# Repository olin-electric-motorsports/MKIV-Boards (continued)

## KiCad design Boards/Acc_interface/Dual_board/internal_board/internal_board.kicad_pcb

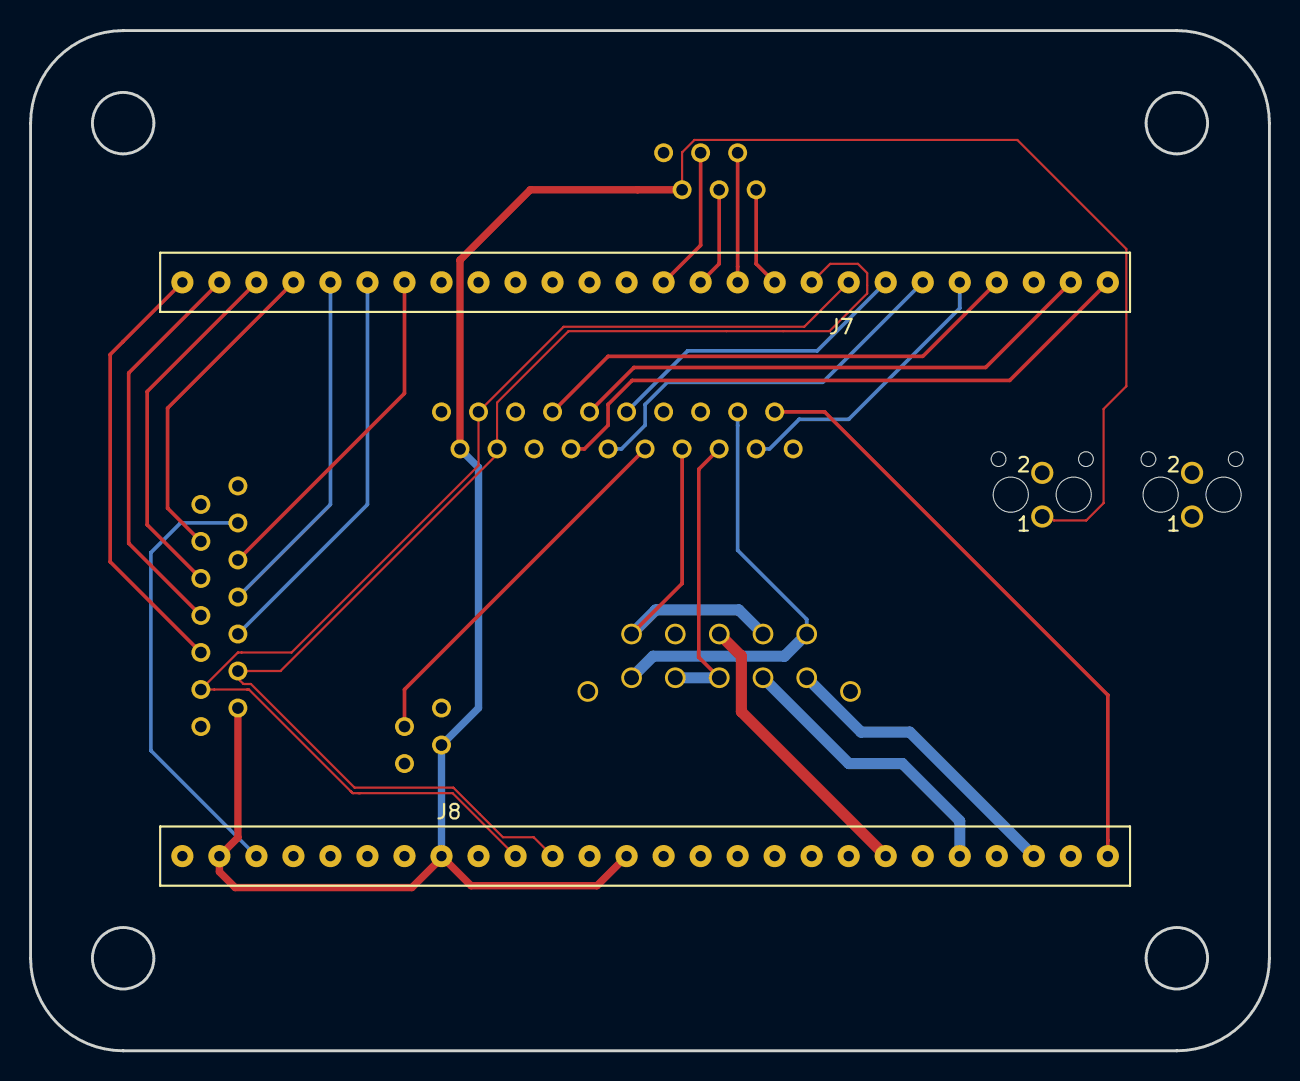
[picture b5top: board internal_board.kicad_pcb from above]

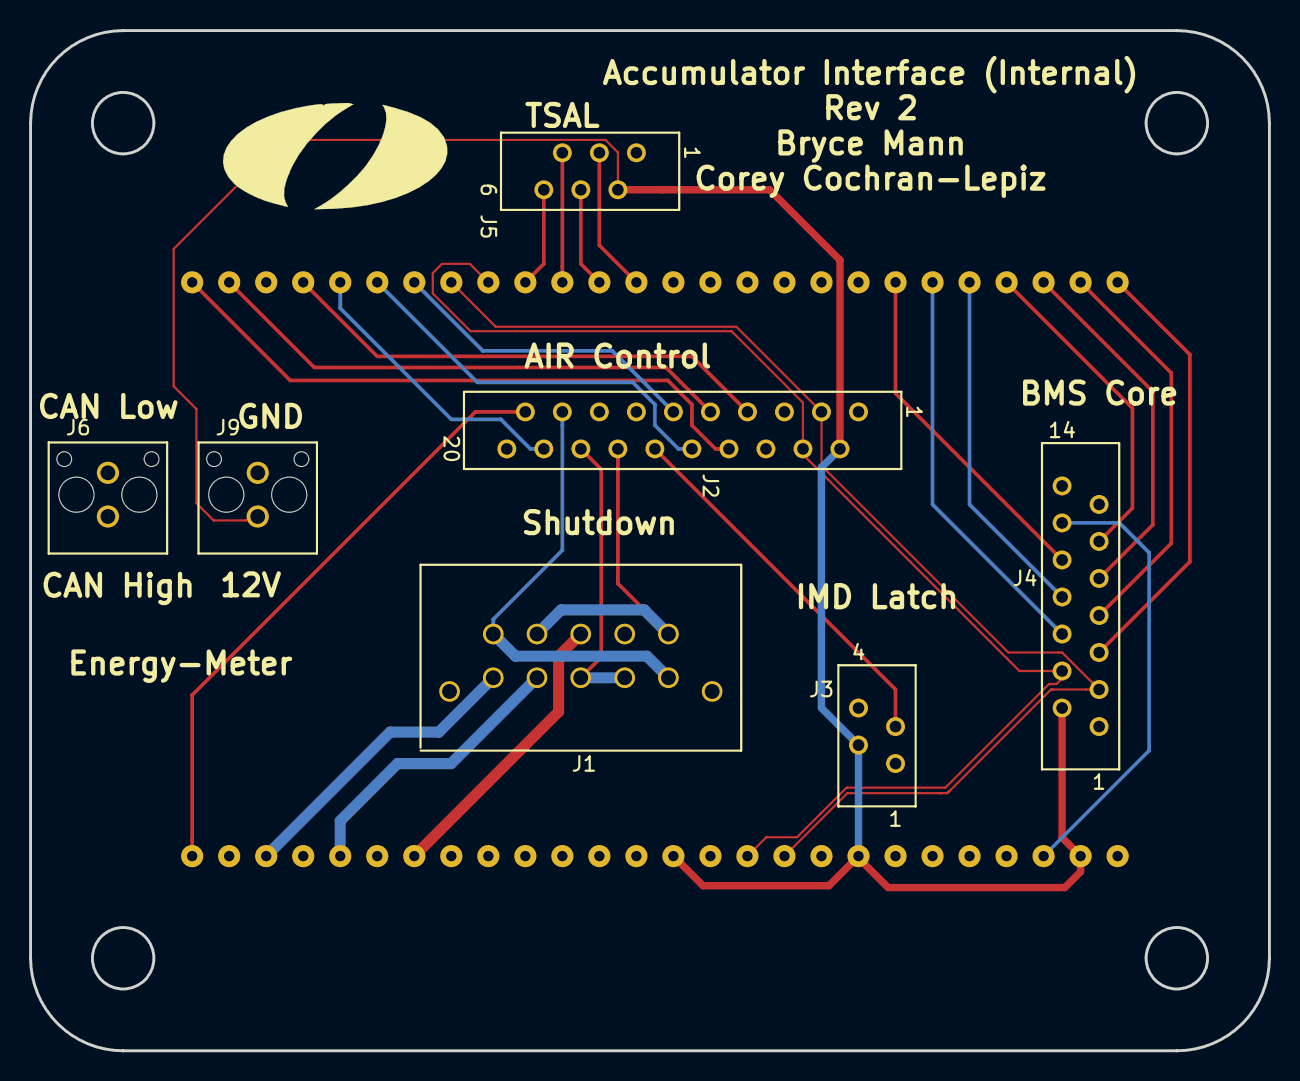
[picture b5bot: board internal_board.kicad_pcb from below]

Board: 4 copper layers, 85.0 x 70.0 mm, 9 parts (7 on the bottom side), 35 nets.

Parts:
J1: MicroFit_VT_10
J2: MM_F_RA_20; micromatch_female_ra_20
J3: MM_F_RA_04; micromatch_female_ra_4
J4: MM_F_RA_14; micromatch_female_ra_14
J5: MM_F_RA_06; micromatch_female_ra_6
J6, J9: MicroFit_V_2
J7, J8: SS-126-G-2; 26pos_screwsocket_.1in

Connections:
/5V_AIR: J2.5, J2.18, J7.5, J8.16
/5V_BMS: J4.5, J7.26
/12V: J2.2, J3.2, J4.2, J5.2, J8.2, J8.8, J8.13, J9.1
/BMS_SENSE: J2.13, J4.13
/BSPD_Current_sense: J4.14, J8.4
/CAN_HIGH: J2.3, J4.3, J7.8, J8.10
/CAN_LOW: J2.4, J4.4, J7.9, J8.11
/Cooling_pressure_sense: J2.19, J8.26
/FAN_PWM: J4.12, J8.3
/IMD_SENSE: J2.12, J3.3
/LED1_AIR: J2.10, J7.6
/LED1_BMS: J4.10, J7.20
/LED2_AIR: J2.11, J7.7
/LED2_BMS: J4.11, J7.23
/MISO_AIR: J2.7, J7.4
/MISO_BMS: J4.7, J7.25
/MOSI_AIR: J2.6, J7.3
/MOSI_BMS: J4.6, J7.21
/RESET_AIR: J2.9, J7.2
/RESET_BMS: J4.9, J7.24
/SCK_AIR: J2.8, J7.1
/SCK_BMS: J4.8, J7.22
/Shutdown_BMS: J1.2, J1.5, J2.14
/Shutdown_E-STOP: J1.7, J8.22
/Shutdown_Final: J1.3, J8.20
/Shutdown_HVD: J1.8, J1.9, J2.16
/Shutdown_IMD: J1.6, J2.15, J8.24
/Shutdown_MP: J1.1, J1.10, J2.17
/TSAL+_G: J5.5, J7.11
/TSAL+_R: J5.3, J7.13
/TSAL-_G: J5.6, J7.10
/TSAL-_R: J5.4, J7.12
/emeter_CAN_HIGH: J6.1, J8.17
/emeter_CAN_LOW: J6.2, J8.19
GND: J1.4, J2.1, J2.20, J3.1, J3.4, J4.1, J5.1, J8.1, J8.7, J8.9, J8.12, J8.18, J9.2

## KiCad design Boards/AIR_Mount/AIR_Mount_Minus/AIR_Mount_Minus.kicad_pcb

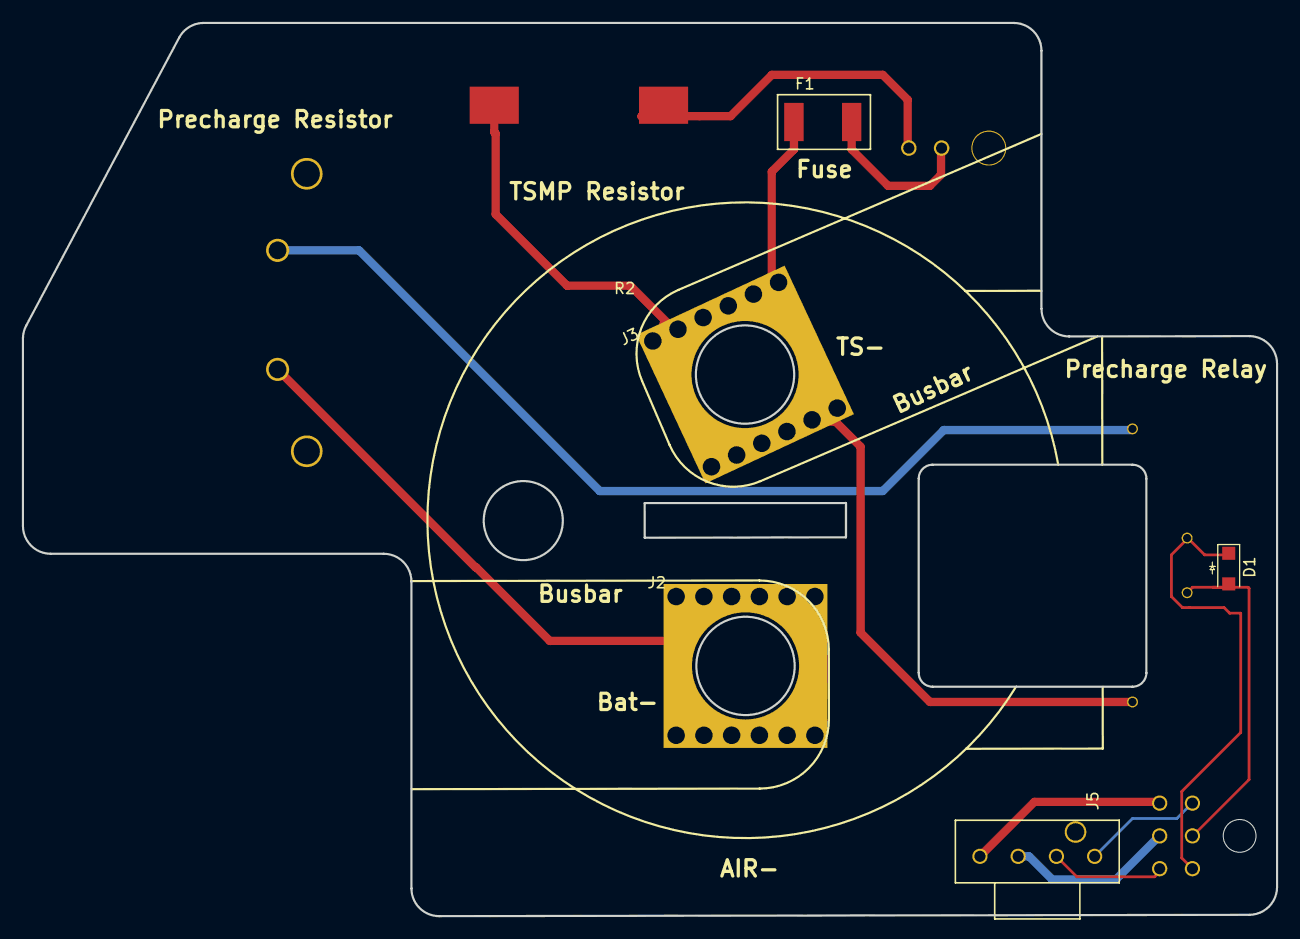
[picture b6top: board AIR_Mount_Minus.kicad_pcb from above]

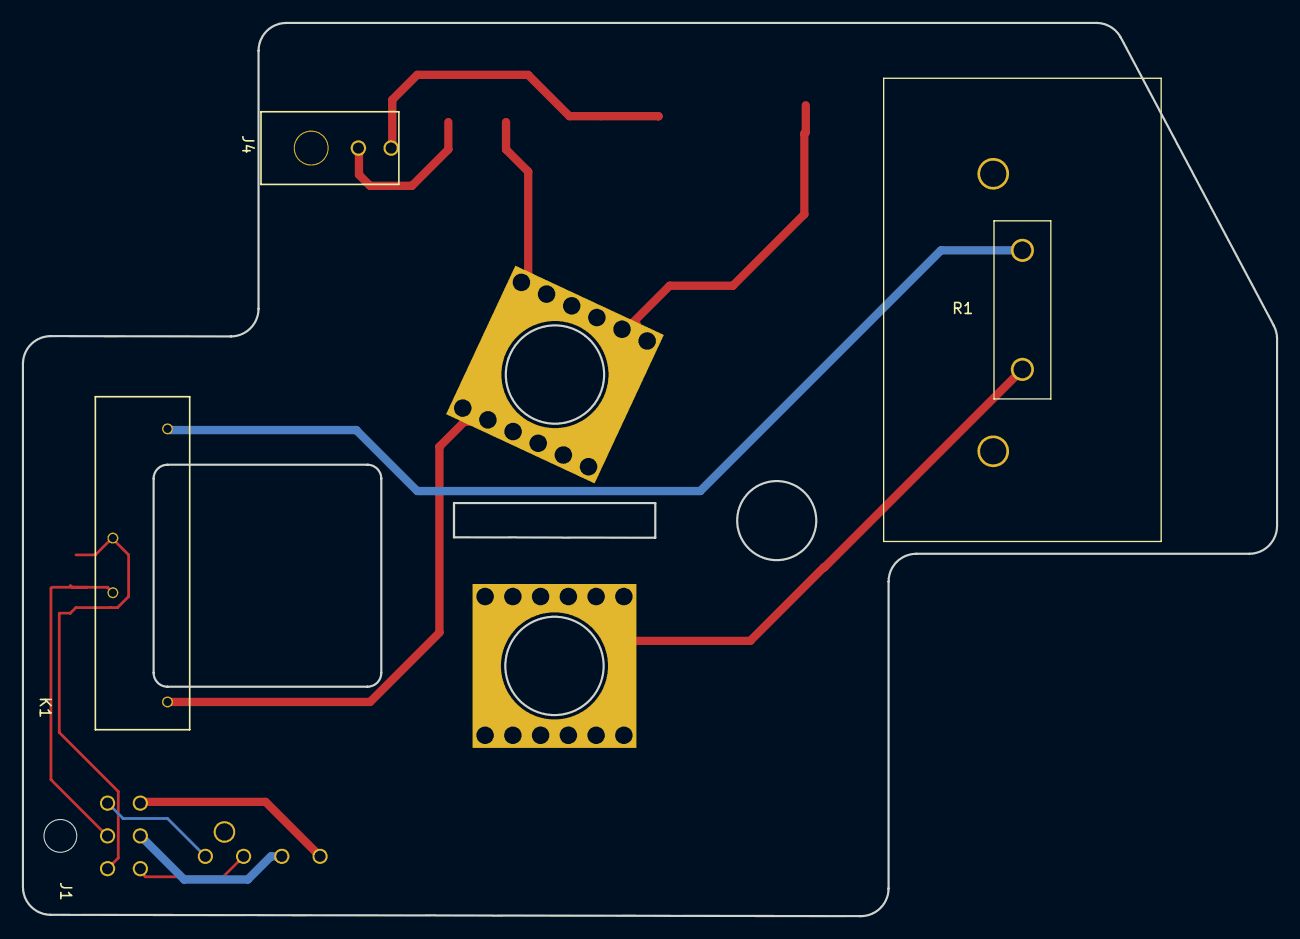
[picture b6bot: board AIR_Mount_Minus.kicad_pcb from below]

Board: 2 copper layers, 114.8 x 81.8 mm, 10 parts (4 on the bottom side), 11 nets.

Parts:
D1: SS110LW; D_SOD-123W_OEM
F1: 200mA_Fuse; Fuse_1812
J1: MicroFit_RA_06
J2, J3: Redcube_7461166
J4: MicroFit_RA_V_2
J5: UF_4_VT; Ultrafit_4
K1: LI12-1A85(NO); Meder-LI12
R1: R_3K_HS; R_3k_HS_TO247
R2: R_10K_Ohmite; 10k_1000V

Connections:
/AUX+: J1.3, J5.1
/AUX-: J1.4, J5.2
/BAT-: J2.1, R1.1
/Coil+: J1.5, J5.3
/Coil-: J1.6, J5.4
/Precharge+: D1.1, J1.1, K1.4
/Precharge-: D1.2, J1.2, K1.3
/TS-: F1.1, J3.1, K1.1, R2.2
/TSMP-: J4.2, R2.1
/TS_Fuse-: F1.2, J4.1
unnamed: K1.2, R1.2

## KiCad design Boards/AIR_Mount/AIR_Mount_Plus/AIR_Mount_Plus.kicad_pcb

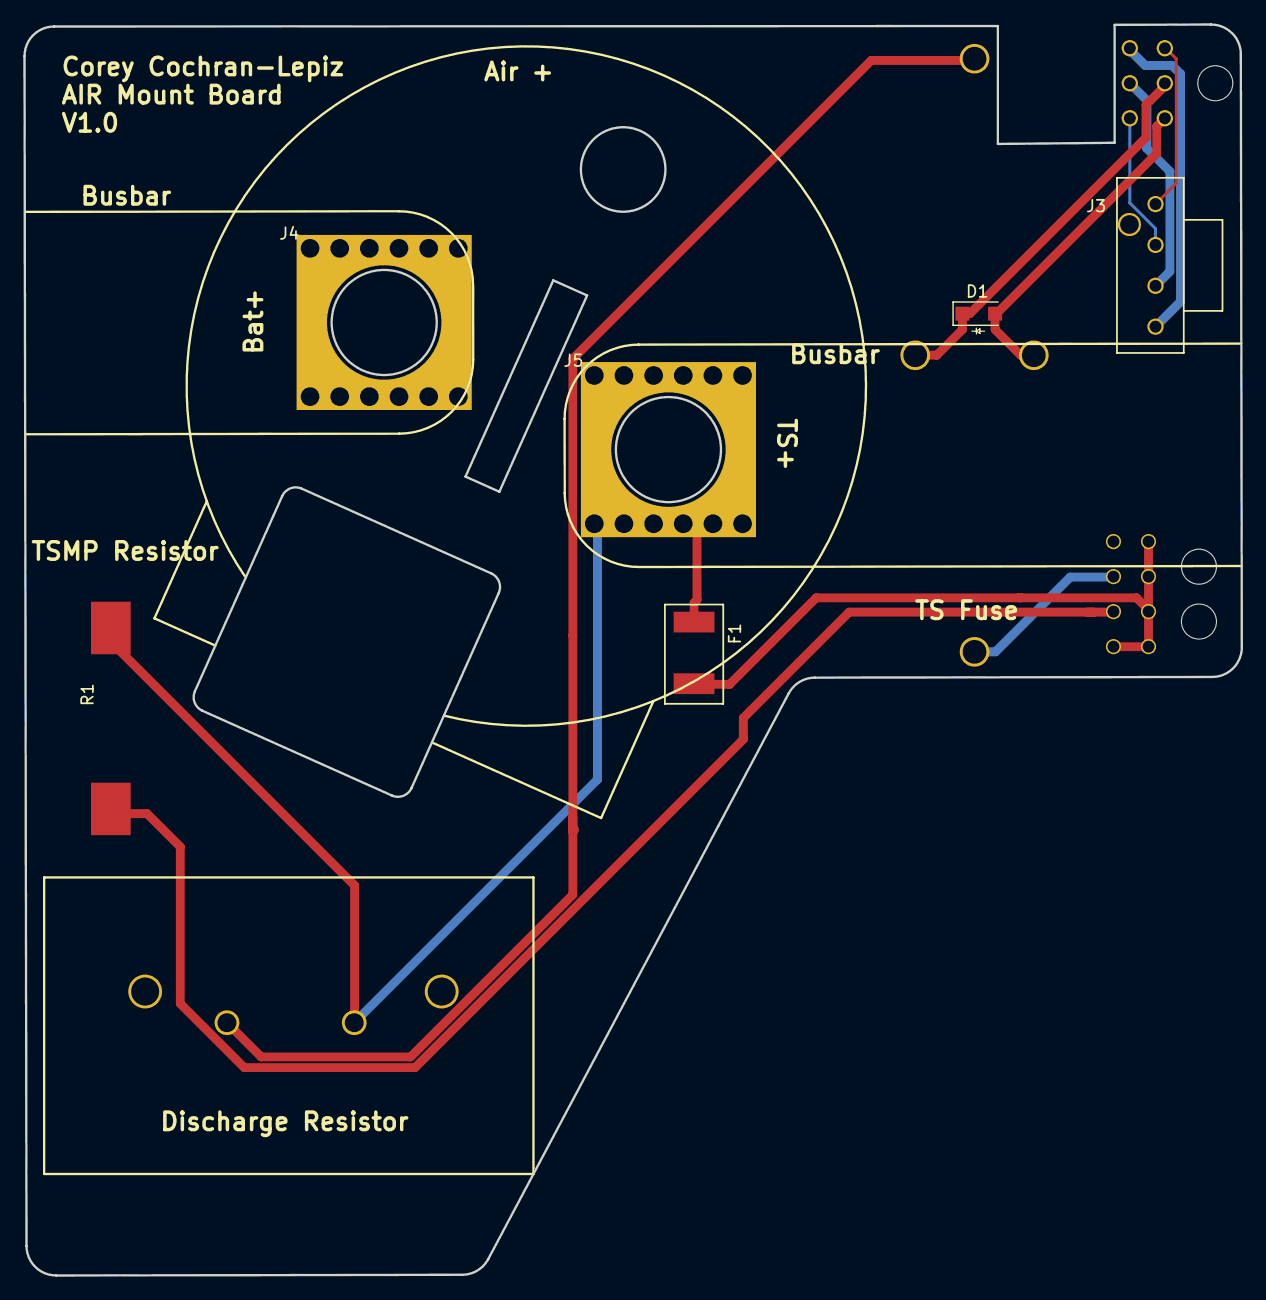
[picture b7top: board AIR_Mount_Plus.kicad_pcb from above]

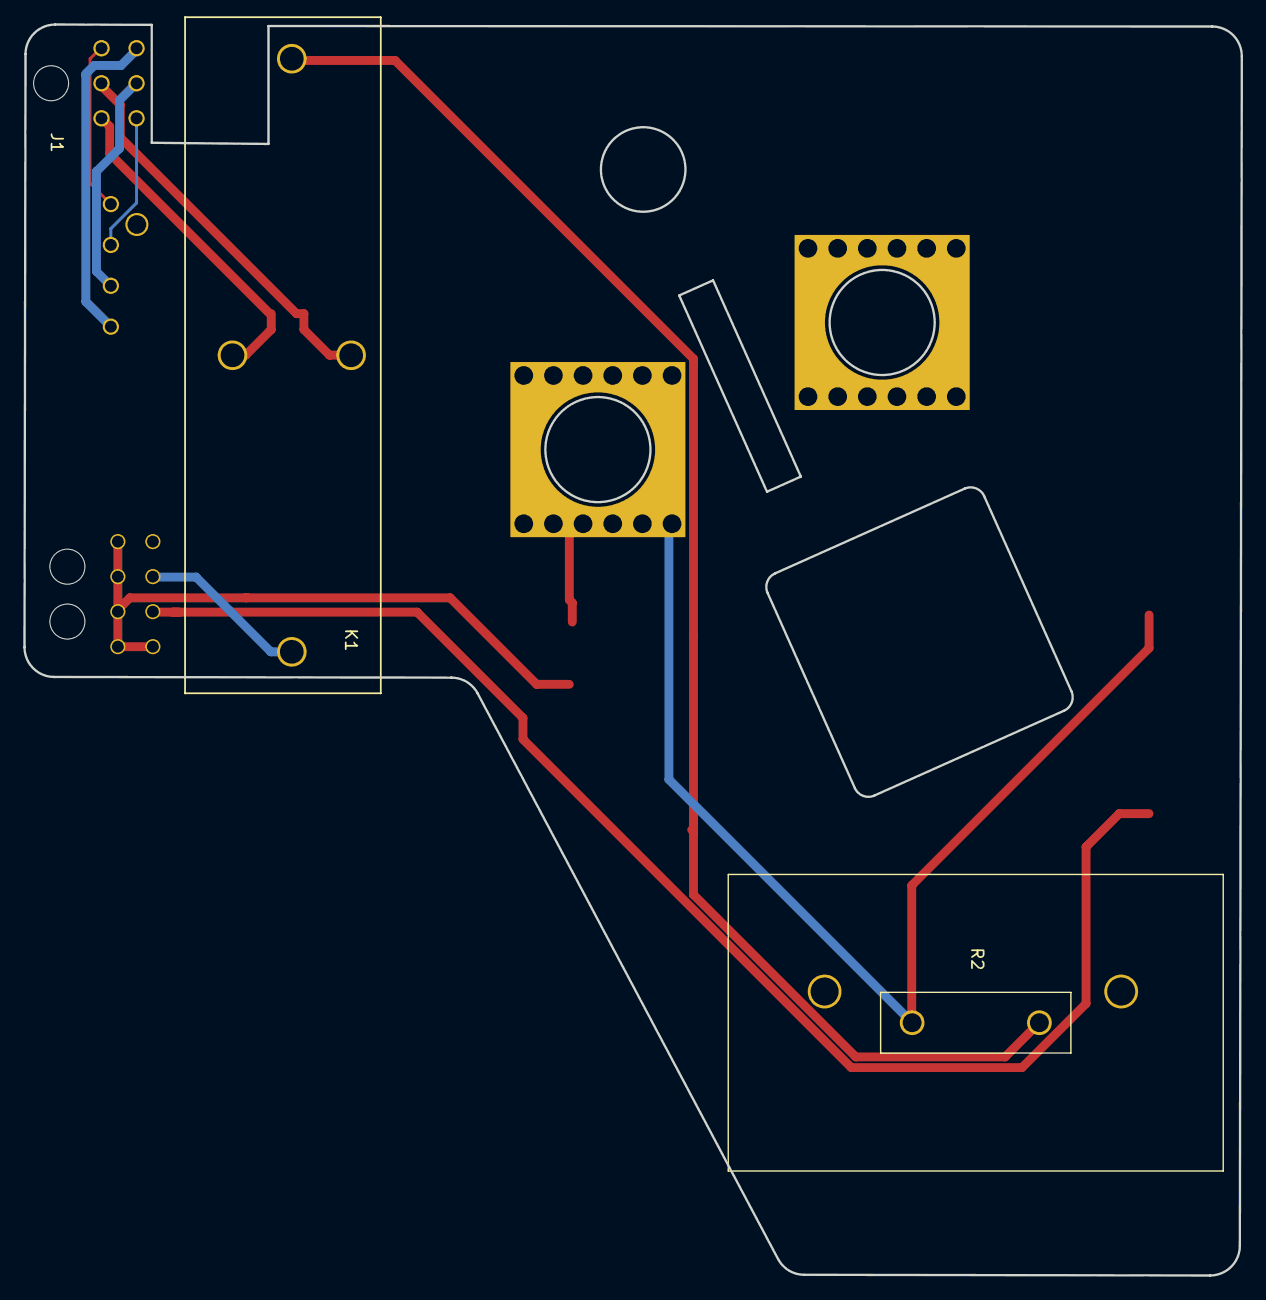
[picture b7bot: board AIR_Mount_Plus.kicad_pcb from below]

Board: 2 copper layers, 104.3 x 107.1 mm, 10 parts (4 on the bottom side), 11 nets.

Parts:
D1: SS110LW; D_SOD-123W_OEM
F1: 200mA_Fuse; Fuse_1812
J1: MicroFit_RA_06
J2: MicroFit_RA_08
J3: UF_4_VT; Ultrafit_4
J4, J5: Redcube_7461166
K1: DBR71210(NC); D-Series_Cynergy_Relay
R1: R_10K_Ohmite; 10k_1000V
R2: R_3K_HS; R_3k_HS_TO247

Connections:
/AUX+: J1.4, J3.2
/AUX-: J1.3, J3.1
/BSPD_Current_Sensor: F1.2, J2.1, J2.2, J2.3, J2.4, J2.5
/Coil+: J1.6, J3.4
/Coil-: J1.5, J3.3
/Discharge_TS+: J2.7, K1.1
/GND: D1.2, J1.1, K1.3
/Shutdown_In: D1.1, J1.2, K1.4
/TS+: F1.1, J5.1, R1.1, R2.1
/TSMP+: J2.6, R1.2
unnamed: K1.2, R2.2

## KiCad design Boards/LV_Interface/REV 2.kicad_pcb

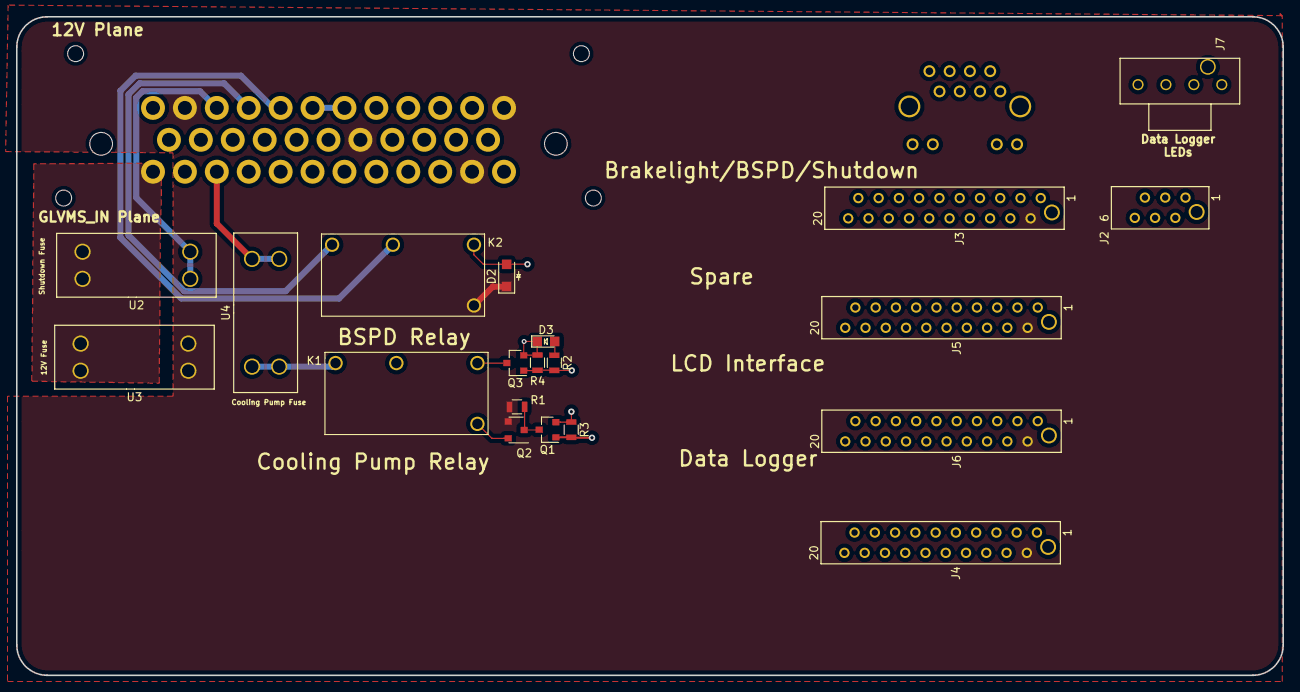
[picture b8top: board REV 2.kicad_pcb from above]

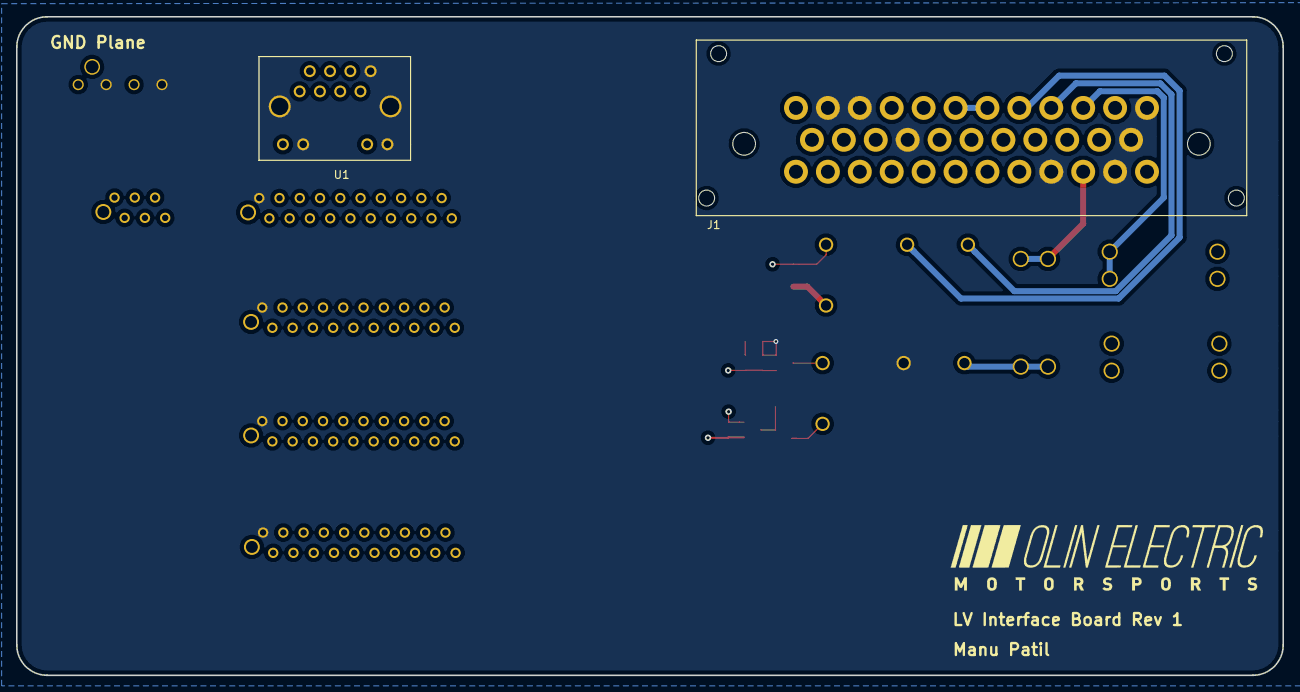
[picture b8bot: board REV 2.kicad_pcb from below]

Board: 4 copper layers, 158.8 x 82.5 mm, 22 parts (2 on the bottom side), 35 nets.

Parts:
D2: SS110LW; D_SOD-123W_OEM
D3: LED_0805; LED_0805_OEM
J1: Ampseal_35_VT; Ampseal_35
J2: MM_F_VT_06; micromatch_female_vert_6
J3, J4, J5, J6: MM_F_VT_20; micromatch_female_vert_20
J7: CONN_01x04; Ultrafit_4
K1, K2: G5Q-1A4-DC5-5V; Relay_SPST_OMRON-G5Q-1A4_OEM
Q1, Q3: SSM3K333R; SOT-23F
Q2: BSS308PE; SOT-23-3_OEM
R1, R2: R_1K; R_0805_OEM
R3, R4: R_10K; R_0805_OEM
U1: RJ45_VT; RJ45-Vertical
U2, U3, U4: Fuse_Holder_Blade; Fuse_Block_Holder

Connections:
/5V: J1.19, J1.30, J3.8, Q1.1, R3.2, U1.7
/12V: D2.1, J1.1, J1.11, J1.17, J1.25, J3.2, J4.2, J5.2, J6.2, K2.5, Q2.2, R1.2, U3.2
/BSPD -> IS: J1.8, J2.3, K2.2
/BSPD Current Sense: J1.18, J2.5
/BSPD Relay: D2.2, J3.3, K2.1
/BSPD Switch +: J1.20, J3.18
/Brake Pressure +: J1.27, J3.15
/Brake Pressure -: J1.29, J3.17
/Brake Pressure Sense: J1.28, J3.16
/Brake Switch +: J1.13, J3.4
/Brake Switch -: J1.24, J3.5
/Brakelight LSD: J1.26, J3.14
/CAN high: J1.4, J1.14, J1.21, J3.6, J4.3, J5.3, J6.3, U1.2
/CAN low: J1.5, J1.15, J1.22, J3.7, J4.4, J5.4, J6.4, U1.1
/Cooling Pressure Sense: J1.31, J2.6
/Cooling Pump: J1.33, U4.1
/Cooling Pump LSD: J3.13, Q3.1, R2.2, R4.1
/Cooling Pump Relay: K1.3, U4.2
/Estop -> BSPD: J1.9, J2.2, K2.3
/Fuse -> Estop: J1.10, J2.1, U2.2
/GLVMS_IN: J1.35, U2.1, U3.1
/LED 1: J4.5, J7.1
/LED 2: J4.6, J7.3
/MISO: J3.9, U1.5
/MOSI: J3.10, U1.6
/RESET: J3.12, U1.3
/RJ45 LED1: J3.19, U1.10
/RJ45 LED2: J3.20, U1.12
/SCK: J3.11, U1.4
/TSMS -> Final Shutdown: J1.6, J1.7, J2.4, Q1.2, R3.1
GND: D3.1, J1.2, J1.3, J1.12, J1.16, J1.23, J1.32, J1.34, J3.1, J4.1, J5.1, J6.1, J7.2, J7.4, K1.2, Q3.2, R4.2, U1.8, U1.9, U1.11, U1.13, U1.14
unnamed: D3.2, R2.1
unnamed: K1.1, Q3.3
unnamed: K1.5, Q2.3
unnamed: Q1.3, Q2.1, R1.1

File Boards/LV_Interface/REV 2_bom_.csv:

Component,Description,Part,References,Value,Footprint,Quantity Per PCB,Datasheet,MPN,MFN,PurchasingLink
1,"LED, Green, 2.2V, 20mA, 0805",LED_0805,D3,LED_0805,LED_0805_OEM,1,http://www.osram-os.com/Graphics/XPic9/00078860_0.pdf,475-1410-1-ND,DK,https://www.digikey.com/products/en?keywords=475-1410-1-ND
2,DIODE SCHOTTKY 100V 1A SOD123W,SS110LW,D2,SS110LW,D_SOD-123W_OEM,1,http://www.taiwansemi.com/products/datasheet/SS14LW%20SERIES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,SS110LWRVGCT-ND,DK,https://www.digikey.com/product-detail/en/taiwan-semiconduct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
3,Ampseal connector 35 pin vertical,Ampseal_35_VT,J1,Ampseal_35_VT,Ampseal_35,1,http://www.te.com/commerce/DocumentDelivery/DDEController?Ac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,1-776231-1,TE,http://www.te.com/usa-en/product-1-776231-1.html
4,CONN HEADER 4 POS 2.54,CONN_01x04,J7,CONN_01x04,Ultrafit_4,1,https://katalog.we-online.de/em/datasheet/6130xx11121.pdf,732-5317-ND,DK,https://www.digikey.com/product-detail/en/wurth-electronics-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
5,Micro-MaTch connector 6 pin female vertical,MM_F_VT_06,J2,MM_F_VT_06,micromatch_female_vert_6,1,http://www.te.com/commerce/DocumentDelivery/DDEController?Ac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,338068-6,TE,http://www.te.com/global-en/product-338068-6.html
6,Micro-MaTch connector 20 pin female vertical,MM_F_VT_20,J3 J4 J5 J6,MM_F_VT_20,micromatch_female_vert_20,4,http://www.te.com/commerce/DocumentDelivery/DDEController?Ac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,2-338068-0,TE,http://www.te.com/global-en/product-2-338068-0.html
7,"Relay, SPST-NO, Switch 10A/30V, Coil 40mA/5V",G5Q-1A4-DC5-5V,K1 K2,G5Q-1A4-DC5-5V,Relay_SPST_OMRON-G5Q-1A4_OEM,2,http://omronfs.omron.com/en_US/ecb/products/pdf/en-g5q.pdf,Z3632-ND,DK,https://www.digikey.com/product-detail/en/omron-electronics-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
8,"MOSFET, P-channel, 30V, 2A",BSS308PE,Q2,BSS308PE,SOT-23-3_OEM,1,https://www.infineon.com/dgdl/BSS308PE_Rev2.03.pdf?folderId=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,BSS308PEH6327XTSA1CT-ND,DK,https://www.digikey.com/products/en/discrete-semiconductor-p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
9,"MOSFET, N-channel, 30V, 6A",SSM3K333R,Q1 Q3,SSM3K333R,SOT-23F,2,https://drive.google.com/drive/folders/0B-V-iZf33Y4GNzhDQTJZanJRbVk,SSM3K333RLFCT-ND,DK,https://www.digikey.com/product-detail/en/toshiba-semiconduc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
10,"Resistor, 10K, 0.25W, 1%, 0805",R_10K,R3 R4,R_10K,R_0805_OEM,2,http://www.bourns.com/data/global/pdfs/CRS.pdf,CRS0805-FX-1002ELFCT-ND,DK,https://www.digikey.com/products/en?keywords=CRS0805-FX-1002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
11,"Resistor, 1K, 0.25W, 1%, 0805",R_1K,R1 R2,R_1K,R_0805_OEM,2,https://www.seielect.com/Catalog/SEI-rncp.pdf,RNCP0805FTD1K00CT-ND,DK,https://www.digikey.com/products/en?keywords=RNCP0805FTD1K00CT-ND
12,Fuse Holder,Fuse_Holder_Blade,U2 U3 U4,Fuse_Holder_Blade,Fuse_Block_Holder,3,https://www.keyelco.com/userAssets/file/M65p41.pdf,36-3557-2-ND ,DK,https://www.digikey.com/product-detail/en/keystone-electroni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
13,RJ45 ethernet connector vertical,RJ45_VT,U1,RJ45_VT,RJ45-Vertical,1,https://www.amphenolcanada.com/ProductSearch/drawings/AC/MRJ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,MRJ-5481-01-ND,DK,https://www.digikey.com/products/en?keywords=MRJ-5481-01
,,,,,,,,,,
,,,,,,,,,,
,,,,,,,,,,
,,,,,,,,,,
,,,,,,,,,,
Component Groups:,13,,,,,,,,,
Component Count:,22,,,,,,,,,
Fitted Components:,22,,,,,,,,,
Number of PCBs:,1,,,,,,,,,
Total components:,22,,,,,,,,,
Schematic Version:,,,,,,,,,,
Schematic Date:,,,,,,,,,,
BoM Date:,Wed 20 Feb 2019 08:30:59 PM EST,,,,,,,,,
Schematic Source:,/home/manu/Desktop/Formula/MKIV-Boards/Boards/LV_Interface/REV 2.sch,,,,,,,,,
KiCad Version:,Eeschema 5.0.0-fee4fd1~66~ubuntu18.04.1,,,,,,,,,

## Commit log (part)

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2018-07-29 set up repo structure
2018-08-09 First pass at schematic
2018-08-12 added new folder for MKIII IMU board
2018-08-13 finished schematic for MKIII IMU board
2018-08-13 fix symbol displaying problem
2018-08-13 started layout
2018-08-13 changed component path in intro board and fixed merge error in imu.kicad_pcb
2018-08-13 added pdf file of simu schematic
2018-08-16 adding schematic
2018-08-16 update stm32f439bi symbol
2018-08-22 Started layout for Intro
2018-08-24 added layout for buck converter
2018-08-24 finished rough layout of IMU board
2018-09-01 made progress on IMU layout
2018-09-01 add power connections with caps for stm32
2018-09-02 added zipped gerber files and BOM
2018-09-02 breakout stm32 ports
2018-09-10 Intro Board Updates
    need to add places for towers
    add new connector row
    label programming pins
2018-09-10 Intro Board Update
    Almost done
    Pending review
2018-09-21 Uploading GERBER files
2018-09-27 Updated Intro Board
    Added:
    -readability
    -usability
    -snazzyniess
    -clean af
2018-10-02 started sd card dev board
2018-10-03 finished schematic
2018-10-03 minor changes to power leds
2018-10-03 now with annotations!
2018-10-03 Adding BOM for Intro
2018-10-04 made schematic super dank
2018-10-04 updated silk stuff and board size
2018-10-05 add RTC clock source
2018-10-05 ordering components
2018-10-16 Started working on MKIV Trottle Board
2018-10-16 Created wheel speed project
2018-10-20 jtag programming port done, usb next
2018-10-20 rtc, jtag (#11)
    * add RTC clock source
    * jtag programming port done, usb next
2018-10-26 Add BMS peripheral schematic rev 1
2018-10-26 Created schematic and started layout of board
2018-10-30 finally made the main sensing board project correctly
2018-10-30 Update Layout of Board
2018-10-30 Added pot and break disc to schematic
2018-10-30 Created alternate drive mode sense circuit
2018-11-01 Create Wheel Speed folder and files
2018-11-01 Moved some wheel speed files
2018-11-05 added a practice board for people to practice layout. Also a good example of what we want schematics to look like
2018-11-06 Fixed Schematic with ampseal, extra programming LEDS, annotations
2018-11-06 Sorry last one, fixed footprint for ampseal
2018-11-06 IMD v1
2018-11-06 lolll
2018-11-06 testing push functionality
2018-11-06 first draft dashboard
2018-11-06 Fixed the location
2018-11-06 Finished changes to ampseal
2018-11-06 Updating Steering Schematic
2018-11-06 random deleted hidden file
2018-11-09 pushing master changes to my fork
2018-11-09 Added SD Socket and level shifter to schematic
2018-11-10 Completed Rev1 Schematic
2018-11-10 Seperated off board circuits to new schematic, made new folder for rev1
2018-11-13 Added 3 programming LEDs
2018-11-13 Updated schematic
2018-11-14 Update Dashboard
    Finish Schematic Review - Added pdf of rev2,
    added 1 more programming LED, rearranged some
    pins on the MM and ATmega16, added flags for Steering Pot & RJ LEDs
2018-11-16 ACTUALLY finished Rev1 schematic and got it cleared
2018-11-16 Updating schematic back to four seperate button design
2018-11-19 Completed rev3 of layout
2018-11-19 Dashboard Layout v3.1 and v4.0
2018-11-20 Finished REV2 layout
2018-11-20 Minor changes to REV2
2018-11-21 Adding layout and some minor pin changes to schematic
2018-11-22 Updating Labels, C1 and Y1 placements
2018-11-26 Schematic SUbmission IMD Latch
2018-11-27 IMU final schematic, need final check off
2018-11-27 New DXF
2018-11-27 removed keep out silkscreens for bolt holes for fab
2018-11-27 Adding switch for record/no record to SD card
2018-11-28 Added fuses and updated bolt hole tolerancing
2018-11-29 Added REV3.1 Layout
2018-11-30 Adding BSPD files and BrakelightShutdown
2018-11-30 Finishing switch design and adding supporting documents.
2018-11-30 Redesign of layout to include new nanofit connectors
2018-11-30 Cleaned up layout. Ready for layour check in #2
2018-12-01 Created BOM and Gerber files for layout, added PDFs for layout and schematic
2018-12-01 Last Couple Changes
2018-12-02 Fixing some power flags.
2018-12-03 Exported gerbers for structural test rev0; Updated BMS peripheral schematic for 2 temp sensors per module and added connectors
2018-12-04 Updated IMU board
2018-12-04 Re-ordered peripheral and structural PCB connectors for ease of layout, added 5V and GND for temp sensors
2018-12-04 Adding new connector, changing power flags, moving LEDs to pins 26, 27, and 28.
2018-12-04 Created and began work on dash left interface board
2018-12-04 Updated PCB IMU
2018-12-04 Updating Silk Screen Sizes
2018-12-06 Updated CAN end resistor and added BMI088 footprint and other stuff
2018-12-06 Pushing layout check-in changes
2018-12-06 Updated schematic and layout and net list
2018-12-07 Adding Gerber Files
2018-12-07 layout stuffffffffffff
2018-12-08 Working on layout
2018-12-08 updated air control board. fixed some labeling issues
2018-12-10 Updating BrakelightShutdownSchematic
2018-12-10 more layout stuff
2018-12-10 Finishing Provisional Layout
2018-12-11 Fixed some issues with components that are misaligned with grid.
2018-12-12 Adding Capacitor to switch
2018-12-13 Restarting layout
2018-12-16 Finished layout (except cut)
2018-12-16 Got feedback
2018-12-24 More IMU Board pcb stuff
2019-01-03 Initial layout placement for BMS peripheral
2019-01-03 Replaced edge cuts with dxf from mechanical
2019-01-07 connected v- and gnd nets on BMS peripheral schematic
2019-01-08 TSAL/AIL schematic first pass
2019-01-15 Made 3D Model for BMS peripheral board
2019-01-17 TSAL/AIL second pass
2019-01-23 Updating layout
2019-01-24 Added DXFs, made changes to layout
2019-01-25 removed unused net labels from TSAL
2019-01-25 TSAL fourth pass because I refuse to read datasheets
2019-01-25 Adding Olin logo to layout
2019-01-28 More tracing on BMS Peripheral
2019-01-29 Updating BSPD/Brakelight/Shutdown
2019-01-29 Final updates to Rev 1 Board
2019-01-29 Updating BSPD/Shutdown/BrakeLight
2019-01-29 Previous working version of layout file
2019-01-31 More layout
2019-02-01 Adding BOM to Data Logger
2019-02-01 finished first round schematic for air ctrl board
2019-02-01 Worked on BMS structural layout
2019-02-02 Dashboard R Rev 4
2019-02-02 modified air ctrl schematic, made pdf of schematic, started layout
2019-02-02 Updated bms structural layout
2019-02-05 Added interface board
2019-02-05 Structural pcb layout
2019-02-05 BMS Structural PCB Rev0
2019-02-05 Generate BOM for BMS_balancing_test
2019-02-06 Pushing again
2019-02-07 Adding LV Interface Board Schematic
2019-02-08 IMU Layout and footprints
2019-02-08 Structural BMS
2019-02-08 Uploading schematic with resolved issues regarding footprints and creation of PCB layout file
2019-02-09 Updated Interface
2019-02-09 Fix symbol links
2019-02-09 Rev1 dashleft layout gerbers
2019-02-09 First Run of Layout, and finished schematic
2019-02-10 finished layout of air ctrl and added new schematic pdf
2019-02-10 added BOM, modified layout slightly, added zip of gerber
2019-02-10 Layout try 3, much less GND islands, and better silkscreen
2019-02-11 Adding LV Interface REV 1
2019-02-12 Resolving merge issue
2019-02-12 Created folder for first revision board and started updated version
2019-02-12 Final COM Board :)))
2019-02-12 Updated both rev4 throttle and rev2 interface
2019-02-12 new gbr file with better annotations
2019-02-12 Adjusted bottom AIL- plane
2019-02-12 Repaired symbol links to formula library
2019-02-13 Resolving merge
2019-02-14 Second pass of PCB with gerber files for shipment
2019-02-19 Updated peripheral board
2019-02-19 Adjusted for design rules
2019-02-19 DXF C for structural PCB
2019-02-20 In process of flipping balancing resistors
2019-02-21 Adding bom and gerber files
2019-02-21 Add CAN, Buck, and Transformer to BMS_core schematic
2019-02-22 Removed the REV folder
2019-02-22 BMS Peripheral thermal pours done!
2019-02-26 Updated Buck Converter Schematic and the Layout for REV2
2019-02-28 Moving DXF to Edge Cuts Layer
2019-03-01 Buck Converter
2019-03-08 single board acc interface second pass
2019-03-08 AIR Mount
    Add prelim files for AIR Mount
    Need to export STEP file for further iteration
    Need to update schmeatic to accurately reflect interface sheet
    Currently in a good place
2019-03-12 Edited files and generated BOM csv for board population
2019-03-12 Update Fuse Holder footprint
2019-03-14 Nanofit footprints switched to zipties
2019-03-14 BMS peripheral finalized after DRC
2019-03-14 Completed Rev1 of LED Bar Backpack
2019-03-16 board update
2019-03-17 Switch out 2018 PWR163 27 ohm balancing resistor for 3.3 ohm
2019-03-18 Update footprints aand 3D models and repair tracing
2019-03-19 replaced IC temp sensors with thermistors and resistors in voltage divider
2019-03-19 Linked footprints for isoSPI cutout properly
2019-03-23 Add gerbers for BMS Core Rev.1
2019-03-24 BMS structural board, revised for thermistors
2019-03-25 Added the .sch, and the .kicad_pcb files required for the buck implementation
2019-03-26 Removing version folders
2019-03-26 removed unnecessary graphic lines
2019-03-26 Add BMS_Peripheral_rev1 3D model
2019-03-26 added silkscreens to bms structural
2019-03-26 Layout changes for level
2019-03-26 added ground plane to single board acc interface
2019-03-26 first pass at dual acc interface boards
2019-03-27 Add BMS core BOM and fix broken components
2019-03-27 More negative layout changes for level
2019-03-27 Reverting to older version of layout
2019-03-28 better connector spacing for the dual board
2019-03-29 Updated the buck converter footprint for implementation
2019-03-29 Updated the pcb layout for the new buck implementation
2019-03-30 Modified Acc Interface
    Fixed micromatch footprints from male to female
    Retraced some lines to fit around footprint
    updated footprints to match library
2019-04-04 Updating PCB that passed DRC with new DXF
2019-04-04 layout!
2019-04-05 moving connectors for Katya
2019-04-09 Deleting the REV2 file for revision control
2019-04-09 IMD Latch Comparator Fix
2019-04-11 IMD DRC checked
2019-04-12 Fixed the C103-Pad1 zone
2019-04-13 Layout and Schematic with microfit v 2
2019-04-13 Add3d board model
2019-04-15 updated air ctrl board and sensing board
2019-04-16 Finished newest rev of Dashboard Right
2019-04-18 Moving micromatch connectors closer to edge and reducing overall size of the board (edgecuts)
2019-04-18 Saving changes made to the board
2019-04-20 updated Pinout fortraces for LEDs and Start Button
2019-04-20 Redo BMS peripheral labels
2019-04-21 Add updated gerbers for BMS Core Rev1.1
2019-04-22 Finish structural re-layout
2019-04-22 Scoot thermistors over
2019-04-22 Add BMS structural rev2 gerb zip
2019-04-22 gerbers with silkscreen for BMS peripheral rev 2.0
2019-04-22 Improved silkscreen
2019-04-24 Edit BMS_core for rev 1.2, couple of small fixes
2019-04-24 Add new gerbers for BMS Core Rev 1.2
2019-04-24 Add compressed gerber archive for BMS_core rev 1.2
2019-04-24 Add Rev 2 Gerber Files
2019-04-24 Update LV INterface Gerber Files
2019-04-24 Moved TSMS->Final Shutdown Trace to Outer Copper Layer
2019-04-28 Updatin g BSPD/Brakelight/Shutdown board to relocate shutdown nodes LEDs and implement new buck converter
2019-05-02 Rename and reorganize BMS structural pins and re-locate MM_F_VT_20
2019-05-02 Modify Acc interface and AIR Mount
    Add emeter lines to the dual mounting Accumulator interface boards
    fix resistor on AIR mount board for new 500V rates TSMP resistor
    Exported and shipped both
2019-05-02 Add up to date gerbers for BMS Structural rev3
2019-05-06 Add BMS_core rev 1.3 with plane cutout for HV area
2019-05-13 Generated files to populate board
2019-05-19 Updated BSPD to detect shrt to gnd
    added second opamp and or gate per ESF feedback to meet rules compliance
2019-05-19 timstamp updates
2019-05-19 finished layout with new trigger
    added components and ran clean DRC
